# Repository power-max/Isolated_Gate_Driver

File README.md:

Just a super basic isolated gate driver with onboard unregulated isolated DC-DC converter (SN6505 based).

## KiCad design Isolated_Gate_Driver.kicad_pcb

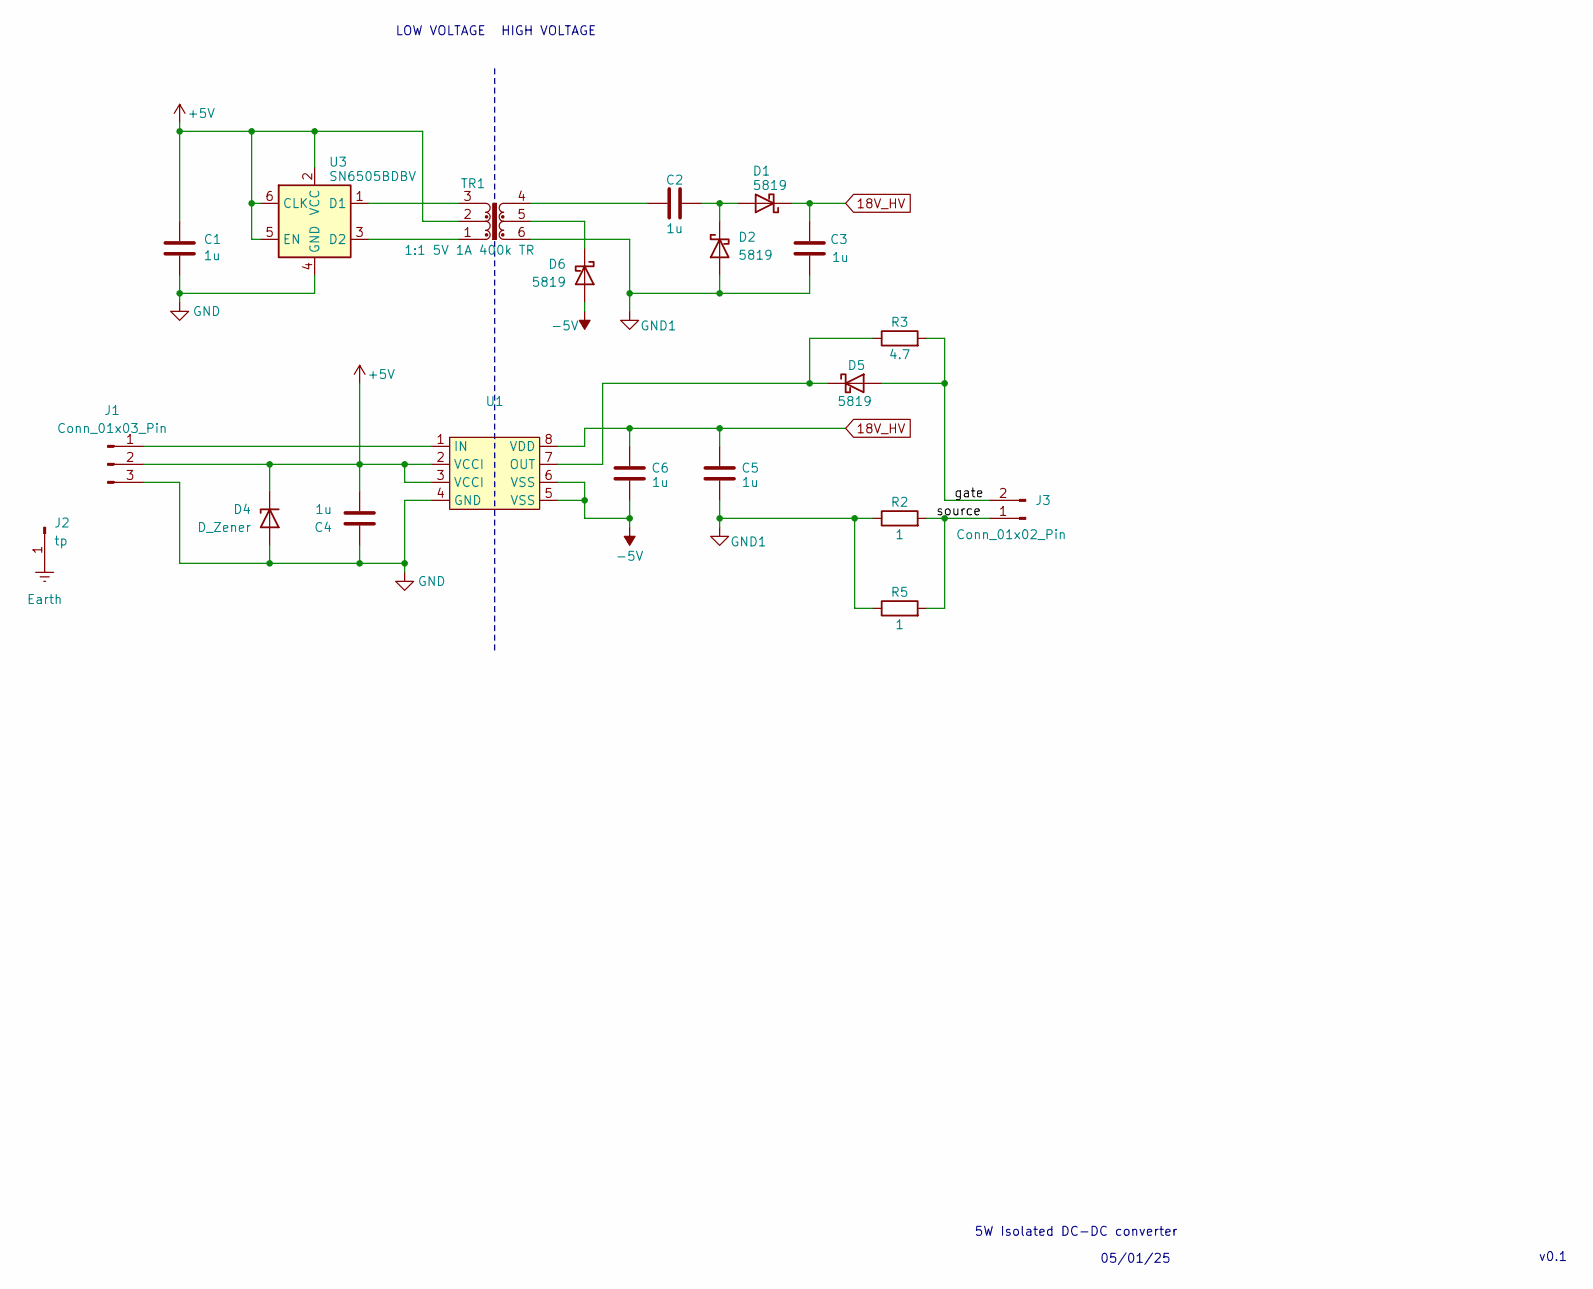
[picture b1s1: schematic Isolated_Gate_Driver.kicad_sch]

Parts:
C1, C2, C3, C4: 1u; C_0603_1608Metric
C5, C6: 1u; C_1206_3216Metric
D1, D2, D5, D6: 5819; D_SOD-123; LCSC C8598
D4: D_Zener; Nexperia_CFP3_SOD-123W
J1: Conn_01x03_Pin; FanPinHeader_1x03_P2.54mm_Vertical
J2: tp; TestPoint_Keystone_5015_Micro_Mini
J3: Conn_01x02_Pin; PinHeader_1x02_P2.54mm_Vertical
R2, R5: 1; R_1206_3216Metric
R3: 4.7; R_1206_3216Metric
TR1: 1:1 5V 1A 400k TR; Pulse_PA2004NL; LCSC C42422416
U1: SSO-8_6.8x5.9mm_P1.27mm_Clearance8mm
U3: SN6505BDBV; SOT-23-6; LCSC C2156022

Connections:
18V_HV: C3.1, C5.2, C6.2, D1.1 (K), U1.8 (VDD)
+5V: C1.2, C4.2, D4.1 (K), J1.2, TR1.2, U1.2 (VCCI), U1.3 (VCCI), U3.2 (VCC), U3.5 (EN), U3.6 (CLK)
-5V: C6.1, D6.2 (A), U1.5 (VSS), U1.6 (VSS)
/gate: D5.2 (A), J3.2, R3.2
/source: J3.1, R2.2, R5.2
Earth: J2.1
GND: C1.1, C4.1, D4.2 (A), J1.3, U1.4 (GND), U3.4 (GND)
GND1: C3.2, C5.1, D2.2 (A), R2.1, R5.1, TR1.6
unnamed: C2.1, TR1.4
unnamed: C2.2, D1.2 (A), D2.1 (K)
unnamed: D5.1 (K), R3.1, U1.7 (OUT)
unnamed: D6.1 (K), TR1.5
unnamed: J1.1, U1.1 (IN)
unnamed: TR1.3, U3.1 (D1)
unnamed: TR1.1, U3.3 (D2)

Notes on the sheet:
HIGH VOLTAGE
LOW VOLTAGE
5W Isolated DC-DC converter
05/01/25
v0.1

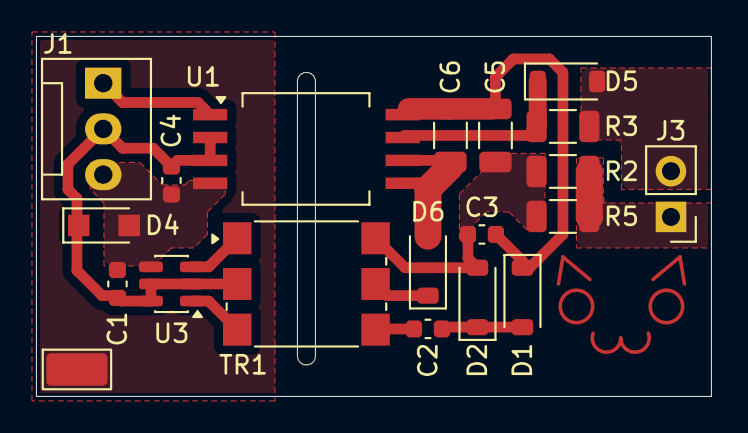
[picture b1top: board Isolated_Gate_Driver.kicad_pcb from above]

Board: 2 copper layers, 37.5 x 20.0 mm, 20 parts (0 on the bottom side), 14 nets.

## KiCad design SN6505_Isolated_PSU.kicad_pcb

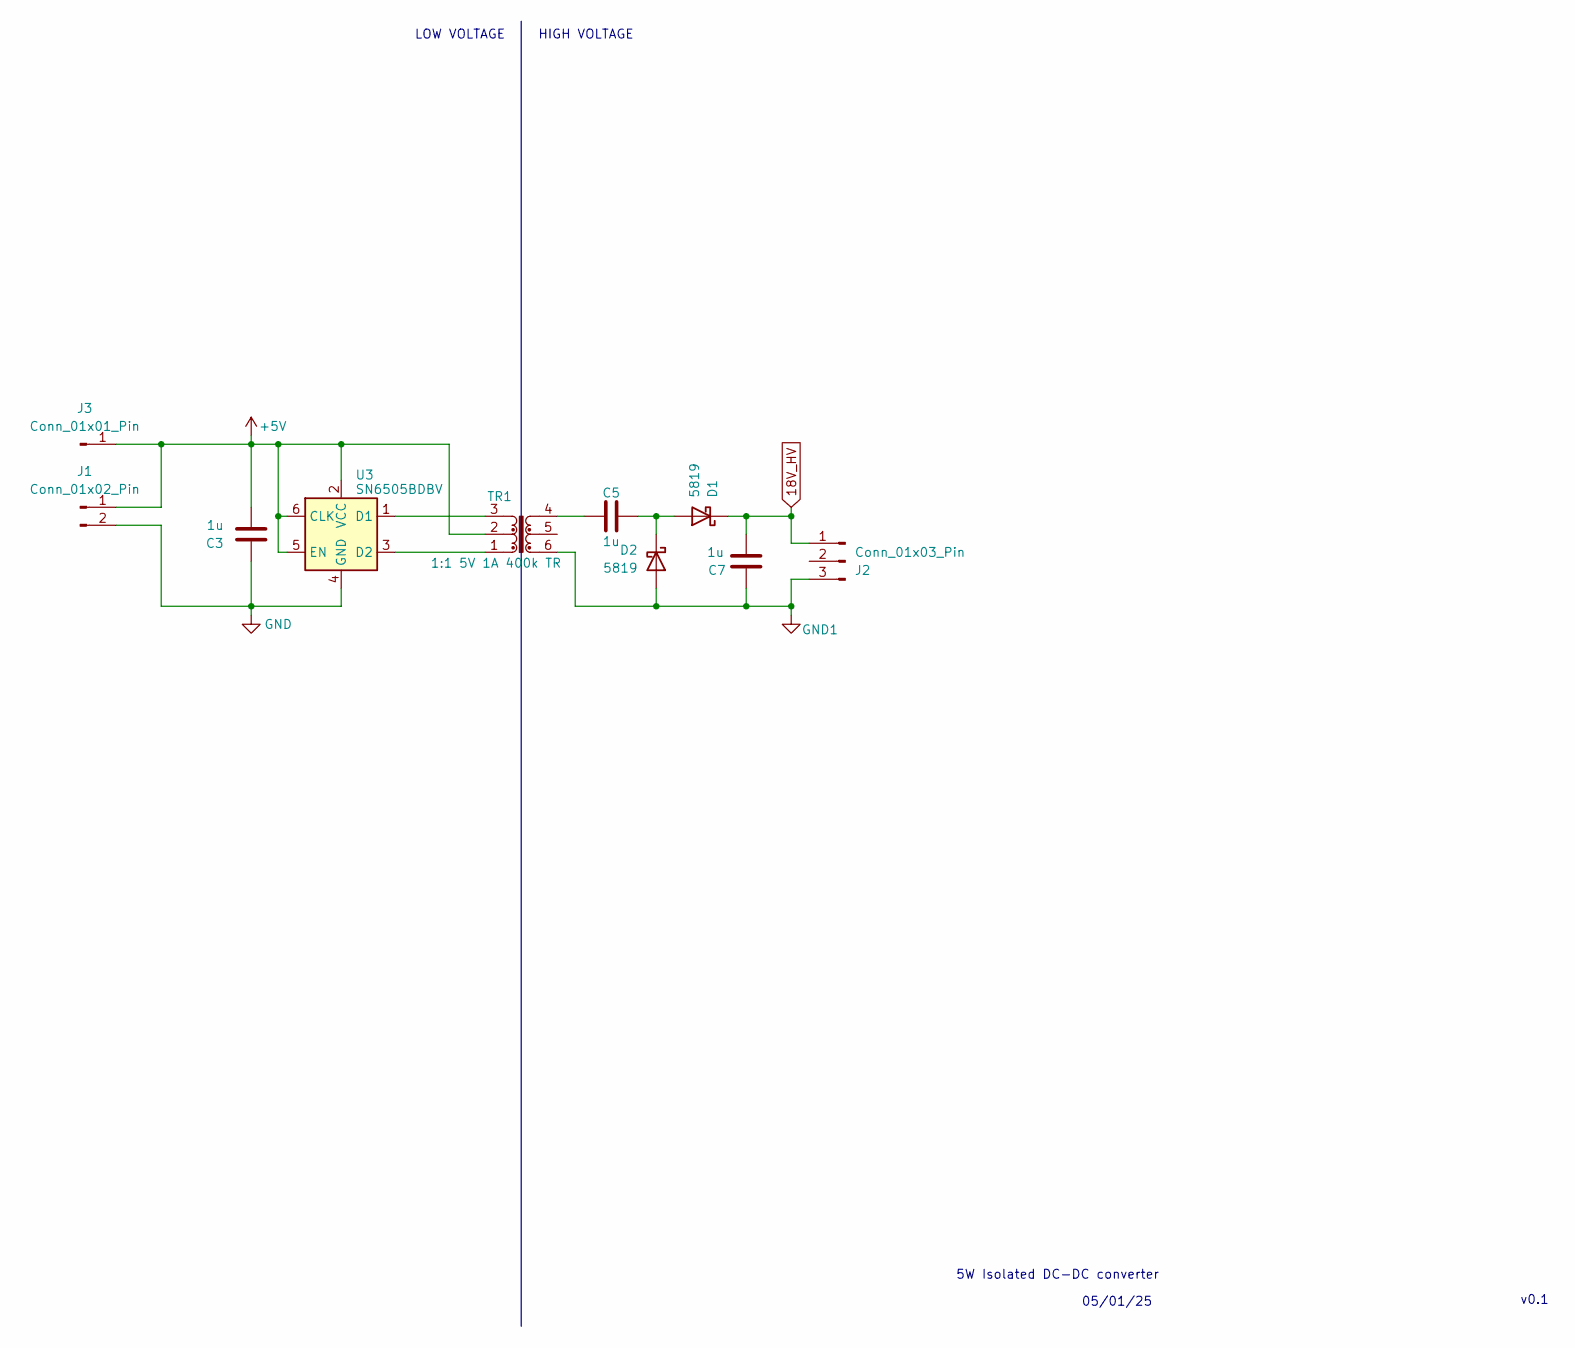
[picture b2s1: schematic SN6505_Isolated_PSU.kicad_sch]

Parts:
C3, C5, C7: 1u; C_0603_1608Metric
D1, D2: 5819; D_SOD-123; LCSC C8598
J1: Conn_01x02_Pin; PinHeader_1x02_P2.54mm_Vertical
J2: Conn_01x03_Pin; PinHeader_1x03_P2.54mm_Vertical
J3: Conn_01x01_Pin; PinHeader_1x01_P2.54mm_Vertical
TR1: 1:1 5V 1A 400k TR; Pulse_PA2004NL; LCSC C42422416
U3: SN6505BDBV; SOT-23-6; LCSC C2156022

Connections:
18V_HV: C7.2, D1.1 (K), J2.1
+5V: C3.2, J1.1, J3.1, TR1.2, U3.2 (VCC), U3.5 (EN), U3.6 (CLK)
GND: C3.1, J1.2, U3.4 (GND)
GND1: C7.1, D2.2 (A), J2.3, TR1.6
unnamed: C5.1, TR1.4
unnamed: C5.2, D1.2 (A), D2.1 (K)
unnamed: TR1.3, U3.1 (D1)
unnamed: TR1.1, U3.3 (D2)

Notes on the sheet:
HIGH VOLTAGE
LOW VOLTAGE
5W Isolated DC-DC converter
05/01/25
v0.1

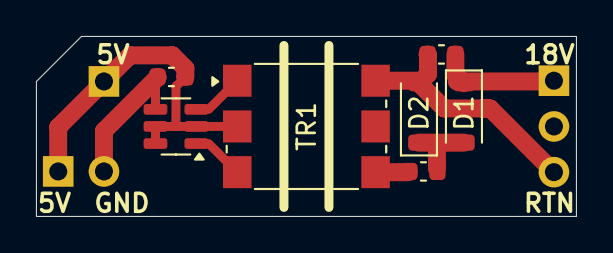
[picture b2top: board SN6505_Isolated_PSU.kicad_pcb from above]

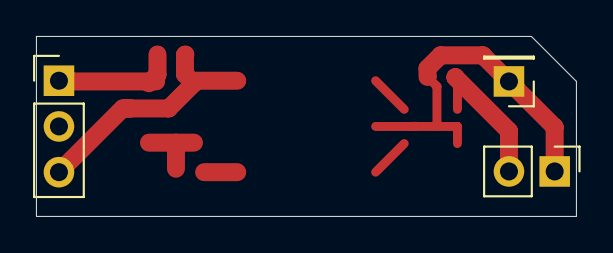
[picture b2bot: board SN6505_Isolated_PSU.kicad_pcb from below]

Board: 2 copper layers, 30.0 x 10.0 mm, 10 parts (3 on the bottom side), 8 nets.

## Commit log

2025-05-01 added 3D view and PDF export, cleaned up schematic
2025-12-23 added shielding on low voltage side, HV slots for improved isolation, probably other things that I forgor.
2025-12-23 :uwu:
